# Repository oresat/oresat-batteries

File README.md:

# OreSat Battery Card

This is the battery card for the OreSat system. You can have up to four of these cards in any OreSat system, ID is set by resistors.

## Version History

- v1.0: We don't talk about v1 (EAGLE).
- v2.0: First true pack with 3D printed cell storage. Many small issues (EAGLE).
- v3.0: Flight ready pack, flown 2021-03-15 on OreSat0. Worked! (EAGLE).
- v3.1: Imported into KiCAD, small tweaks in process (KiCAD).

## Bill of Materials

- [PCBA](https://docs.google.com/spreadsheets/d/11vG1kWyrAjmbF5QJM-EhXmvQoF6O47japwYlHF802do/edit#gid=576852939)
- [Assembly](https://docs.google.com/spreadsheets/d/1GmZE2MR5q2XFSR2Y-65dwwPd7tem3i0CEjZBlCLeJBU/edit?usp=sharing)

## Mechanical CAD

- In [OnShape](https://cad.onshape.com/documents/5eda02ab87dc9021603c3619/w/adac4deb8bbe537007a3b153/e/e3b4fa777f54f6382aedf8d8).

## Technical Information

- 2 independent 2S1P 18650 battery packs (4 batteries total, in 2 packs). Each pack has:
   - Battery protection circuitry for charge and discharge control for each 2S1P pack
   - MAX17500 fuel gauge with cell balancing and cell temperature monitoring
- 3D printed battery holder, designed for CRP Windform SLS Nylon material (OK with Form3 Flame Retardant Resin).
- Positive battery lead disconnection switches (with room for plunger assemblies that go through OreSat +/-X rails).
- Satellite shutdown switches (!SHUTDOWN) (with room for plunger assemblies that go through OreSat +/-X rails).
- Flexible polyimide heater tapes to keep batteries above 0 C
- STM32F091 microcontroller (controlled by the OreSat Power Domain) to interface everything to the CAN bus

## TRANSITION DOCUMENT
Documentation is moving to [Google Docs](https://docs.google.com/document/d/1yaPGtJSM5RQG5k7sVpsDxBkVu4CHtm4LMNnisgOaNRg/edit#heading=h.gjdgxs). The rest of this readme will be integrated later.

## OreSat Vbus
OreSat main power bus is just our 2S Li Ion battery pack, which we've defined as 6.0 V minimum, 7.2 V typical, and 8.4 V maximum. Everything is directly connected to that bus, including:

- Other Oreat battery cards. For >= 2U CubeSats, you'll probably have at least two battery cards.
- All solar panels. Thus the solar panels see the direct battery voltage and can dump directly into the battery packs, thus doing _actual_ MPPT.
- All loads.

## Battery Card Topology
Confusingly, Each OreSat battery card has 2 independent battery packs on it. Each pack is made of a 2S1P 18650 LiPo cell pack. So it's a 2x2S1P if you will. Despite this, each card is independent and the OPD is fully capable of functioning with only one active card.

We decided to separate the packs instead of combining them into a single 2S2P pack for the sake of redundancy, we can lose one cell and the other pack can still provide power to the OPD, as opposed to losing an entire card from a single cell failure.  This design does come with the added drawbacks of extra overhead in the form of requiring more charge protection and fuel gauge circuitry.

## Charge/Discharge Protection
We are using Ablic S8209 to monitor our cell voltage levels and disable charging if the cell voltage goes above the predetermined overcharging threshold or disable discharging if the cell voltage goes below a predetermined discharging threshold.

The S8209 has two inputs that, if activated, will trigger the either the over-charge or under-charge protection to activate.  This allows us to daisy chain these chips together, so that each cell has its own charge protection IC.  It also allows us to connect them to a GPIO on an onboard microcontroller so that we can manually disable charging or discharging functionality if needed.  Below is a state diagram that depicts the desired behavior of our charging and discharging protection circuit

The output of the S8209 uses an internal N-channel MOSFET, which has the potential to latch from radiation exposure.   To combat this, we have P-channel MOSFETS in series with the VDD of each S8209, the gate of the MOSFET is connected to our onboard microcontroller, so that we can periodically power cycle the S8209 and clear the N-channel latch.

The actual control of charge and discharge are done using Linear LTC4412 ideal diode controllers. Totally bizarre, but indepdenently controllable!

## Fuel Gauge and Cell Health Monitoring
Each 2S1P battery back will have two MAX17205 fuel gauges to monitor the packs current state of charge, and the long term health of the battery.  Each MAX17205 will be reporting both the direct State of charge (in mAh) and the percentage over I2C to our M0, compensating for factors such as cell degradation and temperature ranges.  We are still testing the accuracy of the MAX17205's compensation algorithm's for extreme charge levels and temperature in our lab.  At this point we don't know how much we should be relying on these compensation algorithms, they could be amazing! Or horrible! We don't know! Yay science!

Each fuel gauge is also monitoring the battery temperatures with a single internal sensor and two external thermistors (we are still determining the best position for these thermistors).  This gives us a wackton of data which is good because we are data hoarders.

Finally the MAX17205 also does cell balancing, which we'll enable while charging.

## Heaters
Thermal models of both 1U and 2U CubeSats show an average "passive" battery temperature of ~ -10 C). That's not good. We can't charge the battery below 0 C. So we've added heaters to heat up the batteries when charging if necessary.

We're using two Minco HK6903 heaters in parallel. They have "vacuum OK" (apparently?) urethane PSA that we'll use to attach them to the batteries. Note that they're 12.7 x 100 mm, and each heater goes across both batteries. At 49 ohms +/- 10% each, that's 25 ohms in parallel. Unclear on the heater's tempco. We'll ignore for now.

- At 8.4V, that's 336 mA = 2.8 W (at 100% DC)
- At 6.0V, that's 240 mA = 1.4 W (at 100% DC)
- We can of course PWM them and reduce the power as necessary

With that much current draw, we're going to need to modify the OPD circuit breaker to allow more current.

## Batteries

- Tenergy model "30005-0 (ICR 18650-2600, LR1865SK)"
- Rated at 2600 mAh
- Max voltage: 4.2 V
- Typical voltage: 3.6 V
- Minimum voltage: 2.75 V
- Maximum charge current: 1.25 A
   - 0 - 45 C only
- Maximum discharge Current:
   - -20 - 5 C = 1.25 A
   -  5 - 45 C = 5 A
   - 45 - 60 C = 3.75 A

### Temperature

Just to summarize the battery temperature operational range:

- Cell temperature < -20 C -- DEAD
- Cell temperature < 0 C -- DISCHARGE ONLY
- Cell temperature < 45 C -- NORMAL OPERATION
- Cell temperature > 45 C-- DISCHARGE ONLY
- Cell temperature > 60 C-- DEAD

### Cell failure (short)

- Short will plummet battery to < 2.5V (Vlvco) and S-8209 will disconnect the battery from discharging but not charging

## Battery pack behaviors (circuitry + firmware)

- Automatic discharge if > 6.0 V
- Automatic slow charge if < 8.4 V
- Fast charge if battery pack within ~ 0.5 V of other batteries

## Hacking the OPD Circuit Breaker

The OPD circuit breaker is supposed to trip at 300 mA without any division at the current output. Since the headers could pull up to 336, we need to probably go up to that plus 50 mA. So we put in a 10K and 20K to make a 0.66 divider and an N CH MOSFET to turn on the divider on the signal "MOARPWR". Asserting MOARPWR should give you up to 400 mA.

## LICENSE

Copyright Portland State Aerospace Society 2020.

This documentation describes Open Hardware and is licensed under the CERN OHL v. 1.2.

You may redistribute and modify this documentation under the terms of the CERN OHL v.1.2. [http://ohwr.org/cernohl](http://ohwr.org/cernohl). This documentation is distributed WITHOUT ANY EXPRESS OR IMPLIED WARRANTY, INCLUDING OF MERCHANTABILITY, SATISFACTORY QUALITY AND FITNESS FOR A PARTICULAR PURPOSE. Please see the CERN OHL v.1.2 for applicable conditions.

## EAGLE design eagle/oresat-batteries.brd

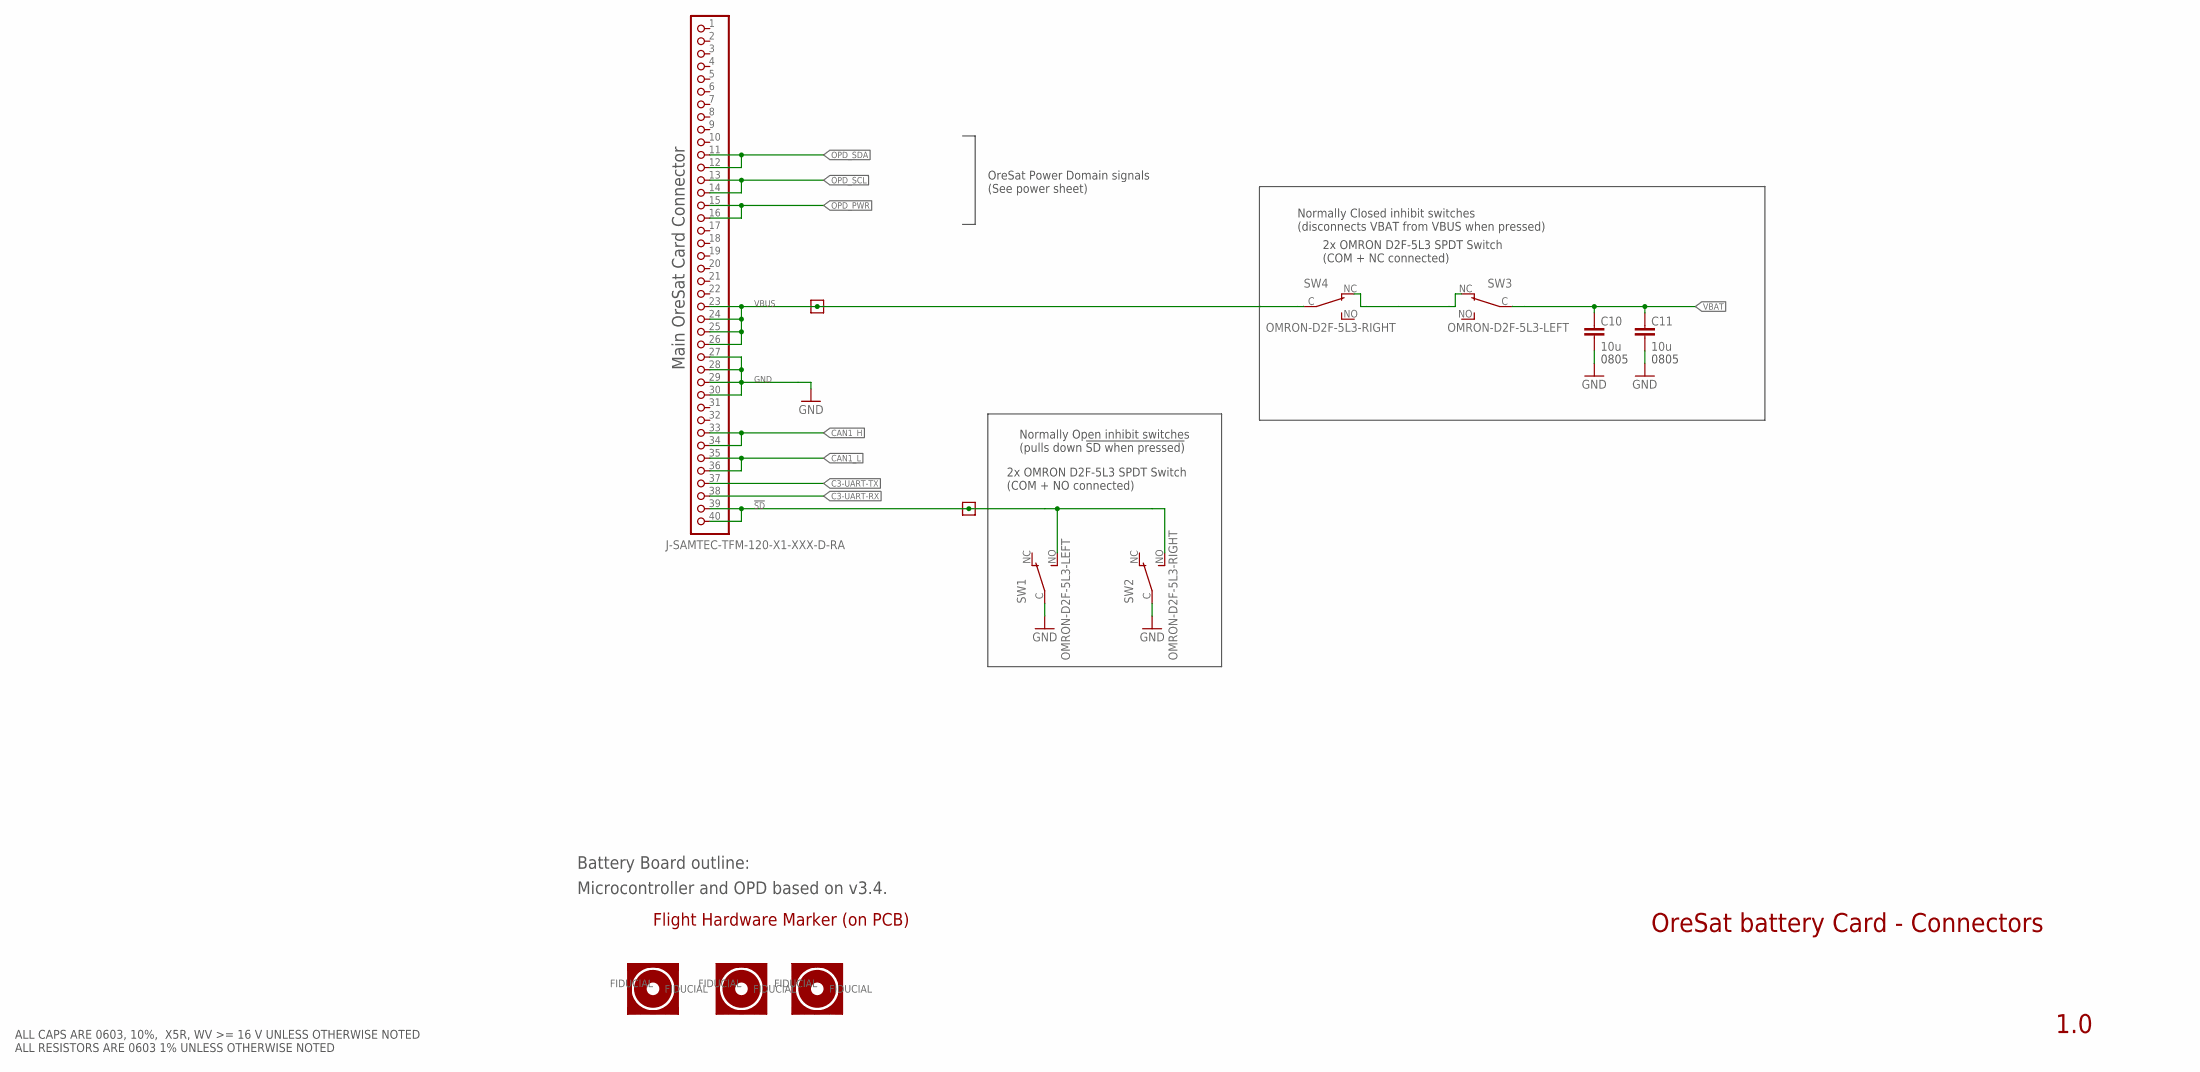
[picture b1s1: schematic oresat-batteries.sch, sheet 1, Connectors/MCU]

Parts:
C10, C11: 10u; .0805-B-NOSILK; MPN CL21A106KOFNNNE
FIDUCIAL1, FIDUCIAL2, FIDUCIAL3: FIDUCIAL-1.0X2.0
J1: J-SAMTEC-TFM-120-X1-XXX-D-RA; MPN TFM-120-01-L-D-RA
SW1, SW3: OMRON-D2F-5L3-LEFT; D2F-L3-D-HORIZONTAL-L
SW2, SW4: OMRON-D2F-5L3-RIGHT; D2F-L3-D-HORIZONTAL-R
TP25, TP57: TEST-POINT-LARGE-SQUARE; 1X01
U$1: FLIGHMARKERNEW; FLIGHTMARKER_NEW_BOARDS

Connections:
!SD: J1.39, J1.40, SW1.NO, SW2.NO, TP57.1; also elsewhere on the board
C3-UART-RX: J1.38; also elsewhere on the board
C3-UART-TX: J1.37; also elsewhere on the board
CAN1_H: J1.33, J1.34; also elsewhere on the board
CAN1_L: J1.35, J1.36; also elsewhere on the board
GND: C10.2, C11.2, J1.27, J1.28, J1.29, J1.30, SW1.C (COM), SW2.C (COM); also elsewhere on the board
INTERSW: SW3.NC, SW4.NC
OPD_PWR: J1.15, J1.16; also elsewhere on the board
OPD_SCL: J1.13, J1.14; also elsewhere on the board
OPD_SDA: J1.11, J1.12; also elsewhere on the board
VBAT: C10.1, C11.1, SW3.C (COM); also elsewhere on the board
VBUS: J1.23, J1.24, J1.25, J1.26, SW4.C (COM), TP25.1; also elsewhere on the board

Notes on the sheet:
OreSat battery Card - Connectors
1.0
Main OreSat Card Connector
OreSat Power Domain signals (See power sheet)
Battery Board outline:
Microcontroller and OPD based on v3.4.
ALL CAPS ARE 0603, 10%, X5R, WV >= 16 V UNLESS OTHERWISE NOTED ALL RESISTORS ARE 0603 1% UNLESS OTHERWISE NOTED
Normally Open inhibit switches (pulls down !SD when pressed)
2x OMRON D2F-5L3 SPDT Switch (COM + NO connected)
Normally Closed inhibit switches (disconnects VBAT from VBUS when pressed)
2x OMRON D2F-5L3 SPDT Switch (COM + NC connected)
0805

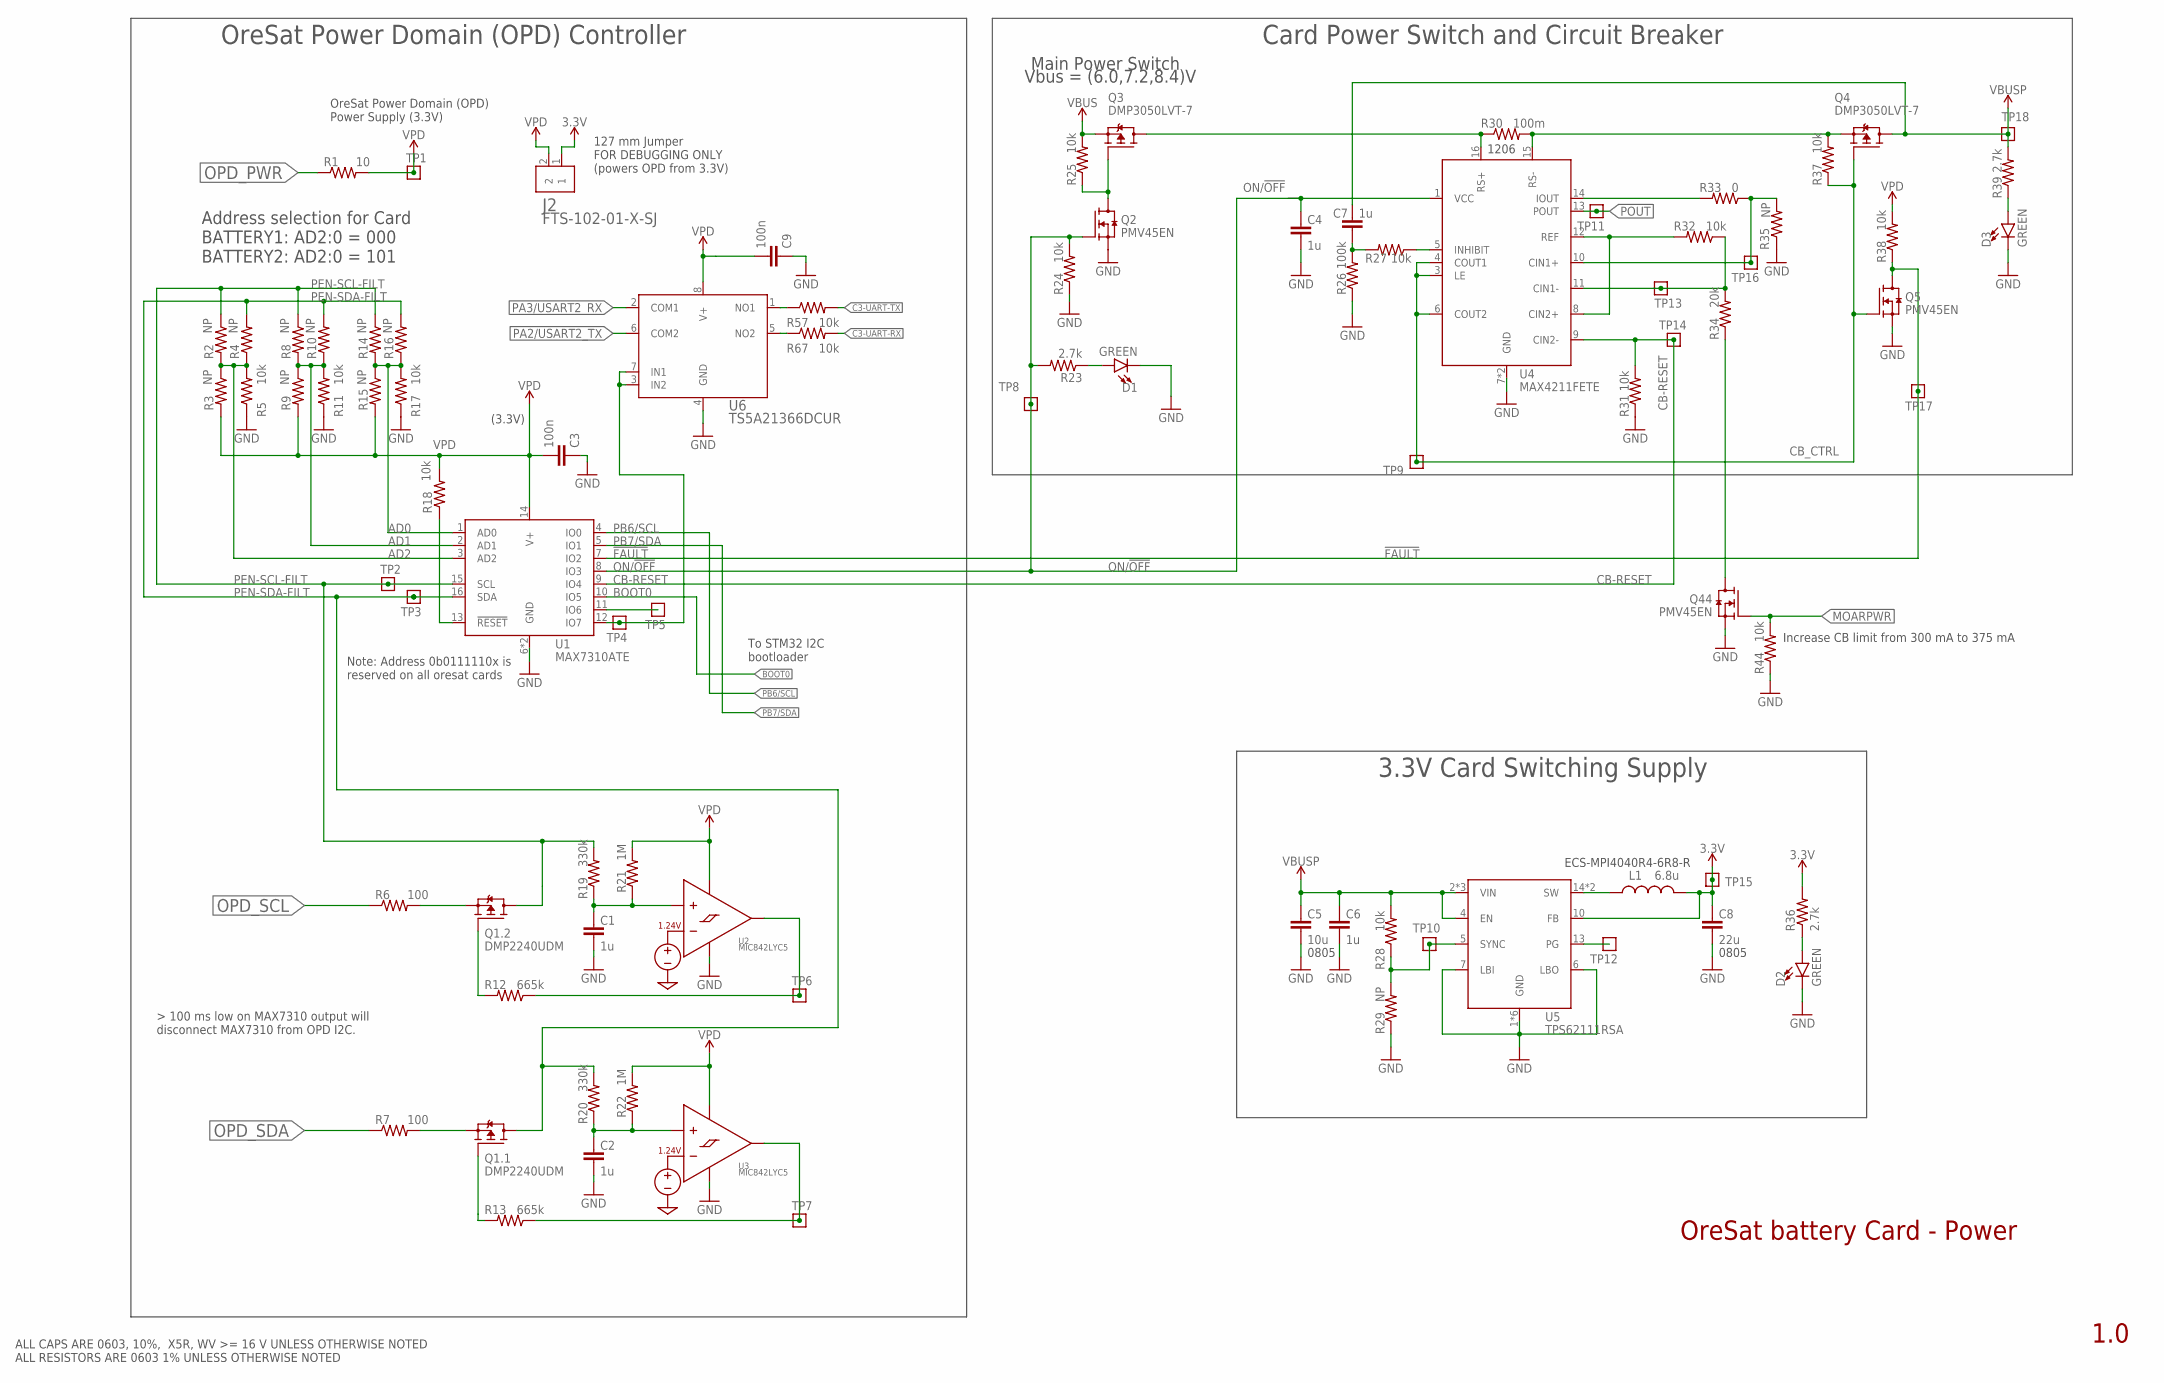
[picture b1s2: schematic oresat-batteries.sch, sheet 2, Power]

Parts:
C1, C2, C4: 1u; .0603-C-NOSILK; MPN CL10B105MO8NNWC
C3, C9: 100n; .0603-C-NOSILK; MPN CL05B104KO5NNNC
C5: 10u; .0805-B-NOSILK; MPN CL21A106KOFNNNE
C6: 1u; .0603-C-NOSILK; MPN CC0603KRX7R7BB105
C7: 1u; .0603-C-NOSILK
C8: 22u; .0805-B-NOSILK; MPN GRM21BR61A226ME51L
D1: GREEN; LED-0603; MPN IN-S63AT5A
D2, D3: GREEN; LED-0603; MPN SML-E12M8WT86
J2: FTS-102-01-X-SJ; SAMTEC-FTS-102-01-X-S
L1: 6.8u; ECS-MPI4040; MPN ECS-MPI4040R4-6R8-R
Q1: DMP2240UDM; SOT23-6; MPN DMP2240UDM
Q2, Q5, Q44: PMV45EN; SOT23-3; MPN PMV45EN2R
Q3, Q4: DMP3050LVT-7; SOT23-6; MPN DMP3050LVT-7
R1: 10; .0603-C-NOSILK; MPN RC0603FR-0710RL
R2, R3, R4, R8, R9, R10, R14, R15, R16: NP; .0603-C-NOSILK; MPN RC0603FR-07665KL
R5, R11, R17, R57, R67: 10k; .0603-C-NOSILK; MPN RC0603FR-07665KL
R6, R7: 100; .0603-C-NOSILK; MPN RC0603FR-07100RL
R12, R13: 665k; .0603-C-NOSILK; MPN RC0603FR-07665KL
R18, R24, R25, R28, R31, R32, R37, R38, R44: 10k; .0603-C-NOSILK; MPN RC0603FR-0710KL
R19, R20: 330k; .0603-C-NOSILK; MPN CRGCQ0603F330K
R21, R22: 1M; .0603-C-NOSILK; MPN RC0603FR-071ML
R23, R36, R39: 2.7k; .0603-C-NOSILK; MPN CRGCQ0603F2K7
R26: 100k; .0603-C-NOSILK; MPN RC1005F6653CS
R27: 10k; .0603-C-NOSILK; MPN RC1005F6653CS
R29, R35: NP; .0603-C-NOSILK; MPN RC1005F6653CS
R30: 100m; 1206-C; MPN CSR1206FTR100
R33: 0; .0603-C-NOSILK; MPN RC0603JR-070RL
R34: 20k; .0603-C-NOSILK; MPN RR0816P-203-D
TP1, TP2, TP3, TP4, TP5, TP6, TP7, TP8, TP9, TP10, TP11, TP12, TP13, TP14, TP15, TP16, TP17, TP18: TEST-POINT-LARGE-SQUARE; 1X01
U1: MAX7310ATE; QFN65P400X400X80-17T210; MPN MAX7310ATE
U2: MIC842LYC5; SC70-5; MPN MIC842LYC5-TR
U3: MIC842LYC5; SC70-5
U4: MAX4211FETE; QFN65P400X400X80-17T210; MPN MAX4211FETE
U5: TPS62111RSA; S-PVQFN-16; MPN TPS62111RSA
U6: TS5A21366DCUR; DCU0008A_N

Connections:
3.3V: C8.1, J2.1, L1.2, R36.2, TP15.1, U5.10 (FB); also elsewhere on the board
!FAULT: Q5.3 (D), R38.1, TP17.1, U1.7 (IO2)
AD0: R14.2, R15.1, R16.1, R17.2, U1.1 (AD0)
AD1: R8.2, R9.1, R10.1, R11.2, U1.2 (AD1)
AD2: R2.2, R3.1, R4.1, R5.2, U1.3 (AD2)
BOOT0: U1.10 (IO5); also elsewhere on the board
C3-UART-RX: R67.2; also elsewhere on the board
C3-UART-TX: R57.2; also elsewhere on the board
CB-RESET: R31.2, TP14.1, U1.9 (IO4), U4.9 (CIN2-)
CB_CTRL: Q4.3 (G), Q5.1 (G), R37.1, TP9.1, U4.3 (LE), U4.4 (COUT1), U4.6 (COUT2)
GND: C1.2, C2.2, C3.1, C4.2, C5.2, C6.2, C8.2, C9.1, D1.C, D2.C, D3.C, Q2.2 (S), Q5.2 (S), Q44.2 (S), R5.1, R11.1, R17.1, R24.1, R26.1, R29.1, R31.1, R35.1, R44.1, U1.6 (GND), U1.EPAD (GND), U2.2 (GND), U3.2 (GND), U4.7 (GND), U4.EPAD (GND), U5.1 (GND), U5.6 (LBO), U5.7 (LBI), U5.9 (GND), U5.11 (GND), U5.12 (GND), U5.16 (GND), U5.PAD (GND), U6.4 (GND); also elsewhere on the board
IOUT1: R33.2, U4.14 (IOUT)
MOARPWR: Q44.1 (G), R44.2; also elsewhere on the board
unnamed: R57.1, U6.1 (NO1)
unnamed: R67.1, U6.5 (NO2)
unnamed: D3.A, R39.1
unnamed: D2.A, R36.1
unnamed: R18.1, U1.13 (!RESET)
unnamed: Q2.3 (D), Q3.3 (G), R25.1
unnamed: Q3.1 (D), Q3.2 (D), Q3.5 (D), Q3.6 (D), R30.1, U4.16 (RS+)
unnamed: Q1.1 (G), R13.2
unnamed: Q44.3 (D), R34.1
unnamed: Q1.3 (G), R12.2
unnamed: R33.1, R35.2, TP16.1, U4.10 (CIN1+)
unnamed: R32.1, R34.2, TP13.1, U4.11 (CIN1-)
unnamed: R32.2, U4.8 (CIN2+), U4.12 (REF)
unnamed: R27.1, U4.5 (INHIBIT)
unnamed: C7.1, R26.2, R27.2
unnamed: Q4.4 (S), R30.2, R37.2, U4.15 (RS-)
unnamed: D1.A, R23.1
unnamed: Q1.5 (S), R7.2
unnamed: R13.1, TP7.1, U3.4 (OUT)
unnamed: TP5.1, U1.11 (IO6)
unnamed: Q1.2 (S), R6.2
unnamed: R12.1, TP6.1, U2.4 (OUT)
unnamed: C1.1, R19.1, R21.1, U2.1 (INP)
unnamed: C2.1, R20.1, R22.1, U3.1 (INP)
unnamed: TP4.1, U1.12 (IO7), U6.3 (IN2), U6.7 (IN1)
ON/!OFF: C4.1, Q2.1 (G), R23.2, R24.2, TP8.1, U1.8 (IO3), U4.1 (VCC)
OPD_PWR: R1.1; also elsewhere on the board
OPD_SCL: R6.1; also elsewhere on the board
OPD_SDA: R7.1; also elsewhere on the board
PA2/USART2_TX: U6.6 (COM2); also elsewhere on the board
PA3/USART2_RX: U6.2 (COM1); also elsewhere on the board
PB6/SCL: U1.4 (IO0); also elsewhere on the board
PB7/SDA: U1.5 (IO1); also elsewhere on the board
PEN-SCL-FILT: Q1.4 (D), R2.1, R8.1, R14.1, R19.2, TP2.1, U1.15 (SCL)
PEN-SDA-FILT: Q1.6 (D), R4.2, R10.2, R16.2, R20.2, TP3.1, U1.16 (SDA)
POUT: TP11.1, U4.13 (POUT); also elsewhere on the board
TPS62111-PG1: TP12.1, U5.13 (PG)
TPS62111-SYNC1: R28.1, R29.2, TP10.1, U5.5 (SYNC)
TPS62111_SW1: L1.1, U5.14 (SW), U5.15 (SW)
VBUS: Q3.4 (S), R25.2; also elsewhere on the board
VBUSP: C5.1, C6.1, C7.2, Q4.1 (D), Q4.2 (D), Q4.5 (D), Q4.6 (D), R28.2, R39.2, TP18.1, U5.2 (VIN), U5.3 (VIN), U5.4 (EN), U5.8 (VIN); also elsewhere on the board
VPD: C3.2, C9.2, J2.2, R1.2, R3.2, R9.2, R15.2, R18.2, R21.2, R22.2, R38.2, TP1.1, U1.14 (V+), U2.5 (VDD), U3.5 (VDD), U6.8 (V+)

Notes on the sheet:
OreSat battery Card - Power
1.0
Main Power Switch
Address selection for Card
(3.3V)
0805
ECS-MPI4040R4-6R8-R
Vbus = (6.0,7.2,8.4)V
OreSat Power Domain (OPD) Power Supply (3.3V)
OreSat Power Domain (OPD) Controller
3.3V Card Switching Supply
Card Power Switch and Circuit Breaker
Note: Address 0b0111110x is reserved on all oresat cards
To STM32 I2C bootloader
1206
ALL CAPS ARE 0603, 10%, X5R, WV >= 16 V UNLESS OTHERWISE NOTED ALL RESISTORS ARE 0603 1% UNLESS OTHERWISE NOTED
Increase CB limit from 300 mA to 375 mA
127 mm Jumper FOR DEBUGGING ONLY (powers OPD from 3.3V)
BATTERY1: AD2:0 = 000 BATTERY2: AD2:0 = 101

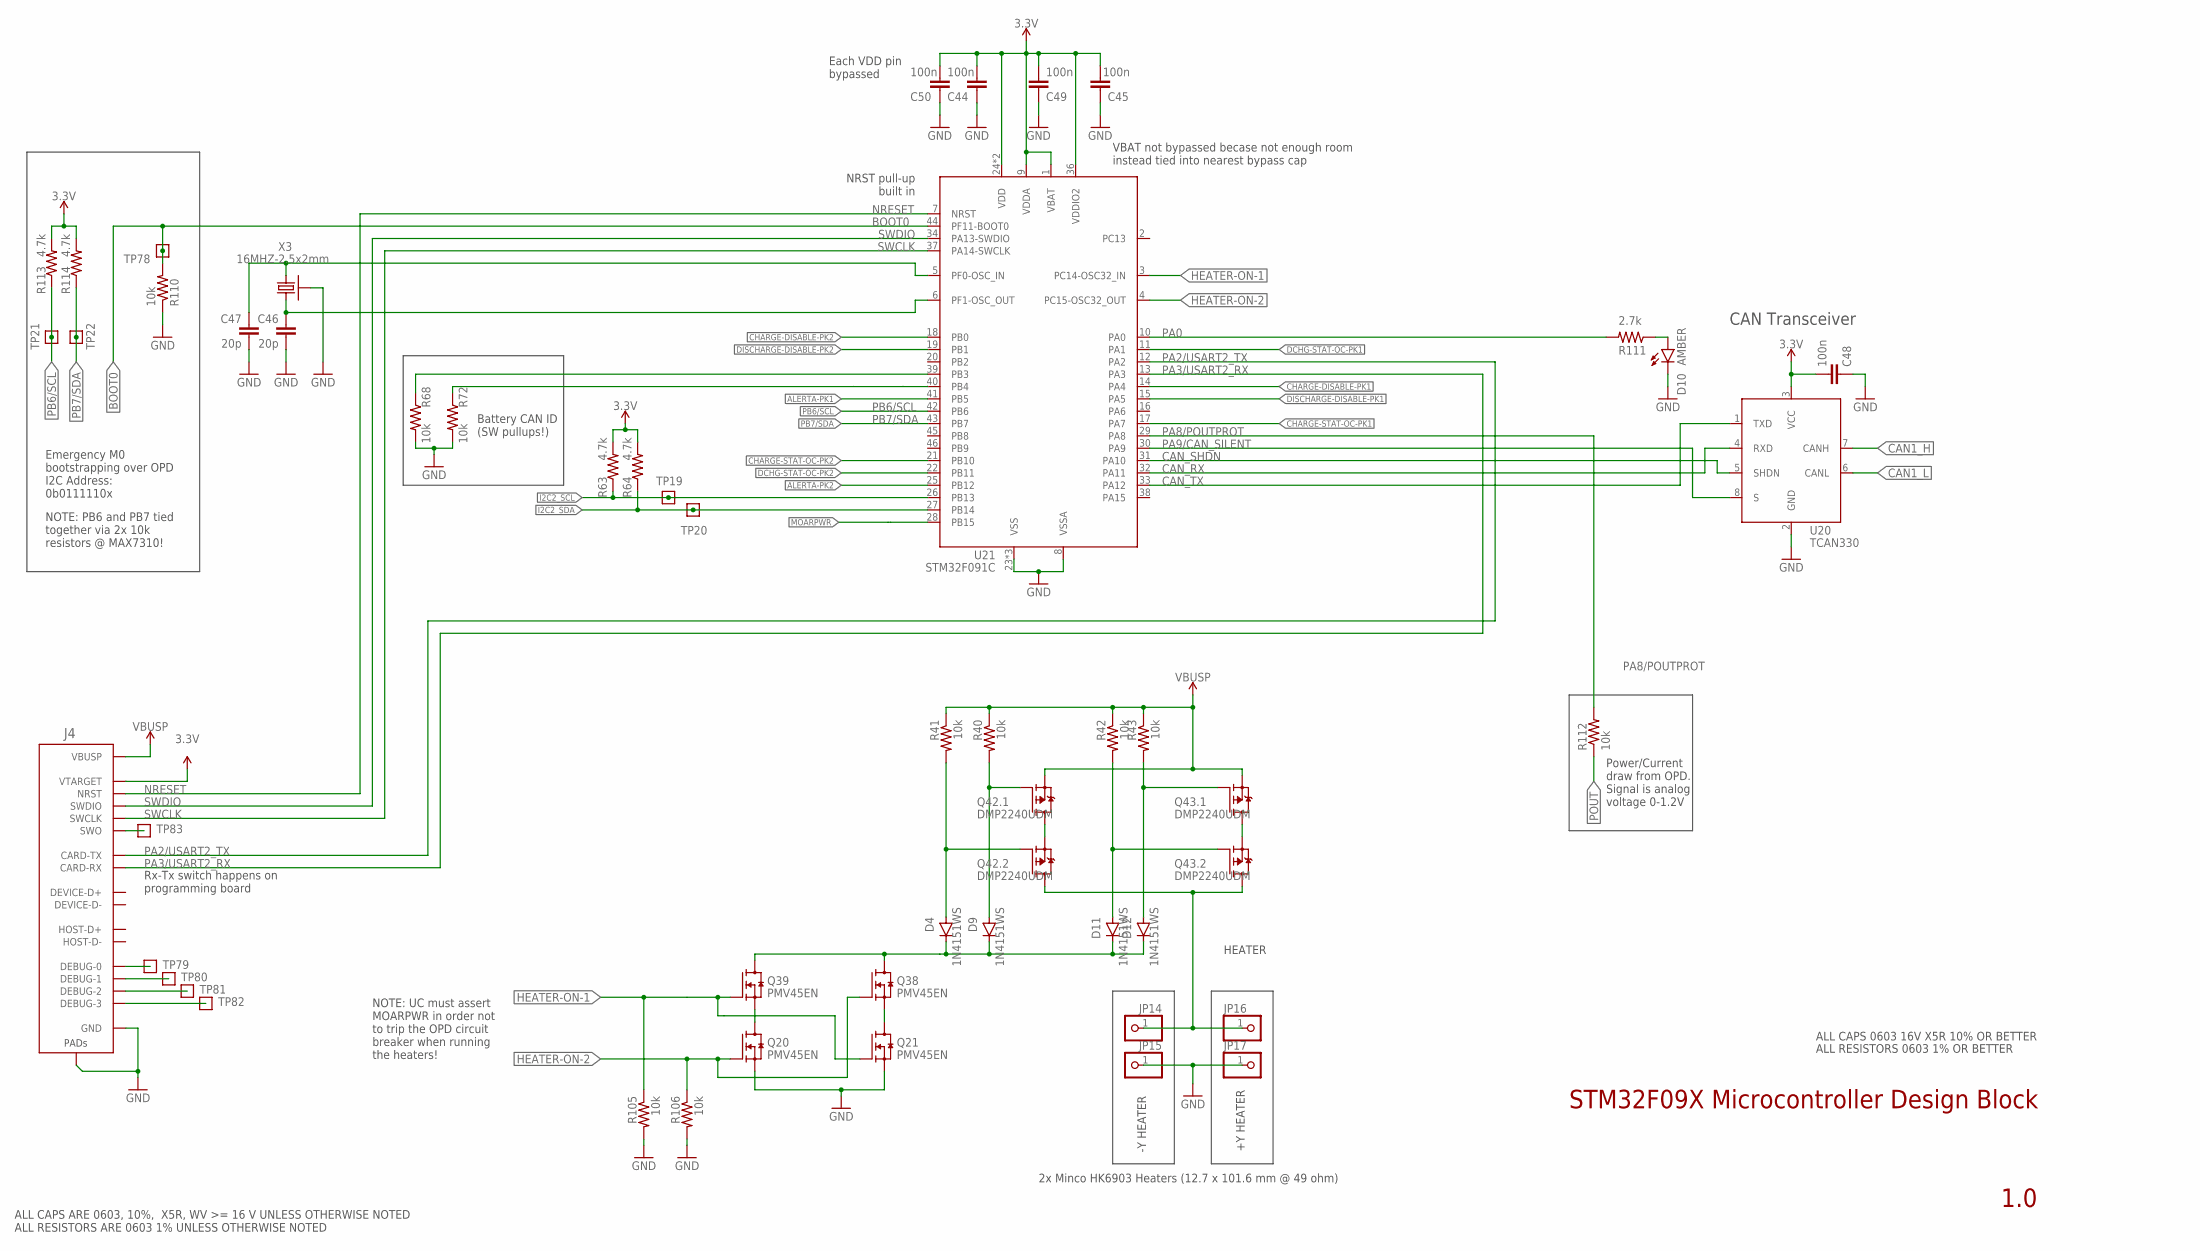
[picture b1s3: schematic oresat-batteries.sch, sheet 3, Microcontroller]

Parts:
C44, C45, C48, C49, C50: 100n; .0603-C-NOSILK; MPN C0603C104M4RACTU
C46, C47: 20p; .0603-C-NOSILK; MPN CC0603JRNPO9BN200
D4, D9, D11, D12: 1N4151WS; SOD323-R; MPN 1N4151WS-E3-08
D10: AMBER; LED-0603; MPN IN-S63AT5A
J4: ORESAT-DEBUG-CONNECTOR-ALL; TE_2-1734592-0; MPN 2-1734592-0
JP14, JP15, JP16, JP17: PINHD-1X1; 1X01
Q20, Q21, Q38, Q39: PMV45EN; SOT23-3
Q42, Q43: DMP2240UDM; SOT23-6
R40, R41, R42, R43, R105, R106, R110, R112: 10k; .0603-C-NOSILK; MPN RC0603FR-0710KL
R63, R64, R113, R114: 4.7k; .0603-C-NOSILK; MPN RR0816P-472-D
R68, R72: 10k; .0603-C-NOSILK; MPN RR0816P-472-D
R111: 2.7k; .0603-C-NOSILK; MPN CRGCQ0603F2K7
TP19, TP20, TP21, TP22, TP78, TP79, TP80, TP81, TP82, TP83: TEST-POINT-LARGE-SQUARE; 1X01
U20: TCAN330; SOT23-8_TI-DCN; MPN TCAN330GDCNT
U21: STM32F091C; MPN STM32F091CBT6
X3: 16MHZ-2.5x2mm; CRYSTAL_2.5X2; MPN ECS-160-10-36Q-ES-TR

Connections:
3.3V: C44.2, C45.2, C48.2, C49.2, C50.2, J4.11 (VTARGET), R63.2, R64.2, R113.2, R114.2, U20.3 (VCC), U21.1 (VBAT), U21.9 (VDDA), U21.24 (VDD), U21.36 (VDDIO2), U21.48 (VDD); also elsewhere on the board
ALERTA-PK1: U21.41 (PB5); also elsewhere on the board
ALERTA-PK2: U21.25 (PB12); also elsewhere on the board
BOOT0: R110.2, TP78.1, U21.44 (PF11-BOOT0); also elsewhere on the board
CAN1_H: U20.7 (CANH); also elsewhere on the board
CAN1_L: U20.6 (CANL); also elsewhere on the board
CAN_RX: U20.4 (RXD), U21.32 (PA11)
CAN_SHDN: U20.5 (SHDN), U21.31 (PA10)
CAN_TX: U20.1 (TXD), U21.33 (PA12)
CHARGE-DISABLE-PK1: U21.14 (PA4); also elsewhere on the board
CHARGE-DISABLE-PK2: U21.18 (PB0); also elsewhere on the board
CHARGE-STAT-OC-PK1: U21.17 (PA7); also elsewhere on the board
CHARGE-STAT-OC-PK2: U21.21 (PB10); also elsewhere on the board
CRYSTALIN2: C47.1, U21.5 (PF0-OSC_IN), X3.1
CRYSTALOUT2: C46.1, U21.6 (PF1-OSC_OUT), X3.3 (2)
DCHG-STAT-OC-PK1: U21.11 (PA1); also elsewhere on the board
DCHG-STAT-OC-PK2: U21.22 (PB11); also elsewhere on the board
DISCHARGE-DISABLE-PK1: U21.15 (PA5); also elsewhere on the board
DISCHARGE-DISABLE-PK2: U21.19 (PB1); also elsewhere on the board
GND: C44.1, C45.1, C46.2, C47.2, C48.1, C49.1, C50.1, D10.C, J4.3 (GND), J4.6 (GND), J4.9 (GND), J4.PAD1 (PAD), J4.PAD2 (PAD), JP15.1, JP17.1, Q20.2 (S), Q21.2 (S), R68.2, R72.2, R105.2, R106.2, R110.1, U20.2 (GND), U21.8 (VSSA), U21.23 (VSS), U21.35 (VSS), U21.47 (VSS), X3.2 (SHIELD), X3.4 (SHIELD); also elsewhere on the board
HEATER: JP14.1, JP16.1, Q42.4 (D), Q43.4 (D)
HEATER-ON-1: Q21.1 (G), Q39.1 (G), R105.1, U21.3 (PC14-OSC32_IN)
HEATER-ON-2: Q20.1 (G), Q38.1 (G), R106.1, U21.4 (PC15-OSC32_OUT)
I2C2_SCL: R63.1, TP19.1, U21.26 (PB13); also elsewhere on the board
I2C2_SDA: R64.1, TP20.1, U21.27 (PB14); also elsewhere on the board
MOARPWR: U21.28 (PB15); also elsewhere on the board
unnamed: D11.A, Q43.3 (G), R42.2
unnamed: D4.A, Q42.3 (G), R41.2
unnamed: Q42.2 (S), Q42.6 (D)
unnamed: Q43.2 (S), Q43.6 (D)
unnamed: R68.1, U21.39 (PB3)
unnamed: D12.A, Q43.1 (G), R43.2
unnamed: D9.A, Q42.1 (G), R40.2
unnamed: D4.C, D9.C, D11.C, D12.C, Q38.3 (D), Q39.3 (D)
unnamed: Q20.3 (D), Q39.2 (S)
unnamed: Q21.3 (D), Q38.2 (S)
unnamed: R72.1, U21.40 (PB4)
unnamed: D10.A, R111.1
unnamed: J4.20 (DEBUG-3), TP82.1
unnamed: J4.19 (DEBUG-2), TP81.1
unnamed: J4.18 (DEBUG-1), TP80.1
unnamed: J4.17 (DEBUG-0), TP79.1
unnamed: J4.16 (SWO), TP83.1
NRESET: J4.10 (NRST), U21.7 (NRST)
PA0: R111.2, U21.10 (PA0)
PA2/USART2_TX: J4.13 (CARD-TX), U21.12 (PA2); also elsewhere on the board
PA3/USART2_RX: J4.12 (CARD-RX), U21.13 (PA3); also elsewhere on the board
PA8/POUTPROT: R112.2, U21.29 (PA8)
PA9/CAN_SILENT: U20.8 (S), U21.30 (PA9)
PB6/SCL: R113.1, TP21.1, U21.42 (PB6); also elsewhere on the board
PB7/SDA: R114.1, TP22.1, U21.43 (PB7); also elsewhere on the board
POUT: R112.1; also elsewhere on the board
SWCLK: J4.15 (SWCLK), U21.37 (PA14-SWCLK)
SWDIO: J4.14 (SWDIO), U21.34 (PA13-SWDIO)
VBUSP: J4.1 (VBUSP), J4.2 (VBUSP), Q42.5 (S), Q43.5 (S), R40.1, R41.1, R42.1, R43.1; also elsewhere on the board

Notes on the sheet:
ALL CAPS ARE 0603, 10%, X5R, WV >= 16 V UNLESS OTHERWISE NOTED ALL RESISTORS ARE 0603 1% UNLESS OTHERWISE NOTED
NRST pull-up built in
CAN Transceiver
1.0
Emergency M0 bootstrapping over OPD I2C Address: 0b0111110x
NOTE: PB6 and PB7 tied together via 2x 10k resistors @ MAX7310!
Power/Current draw from OPD. Signal is analog voltage 0-1.2V
Each VDD pin bypassed
VBAT not bypassed becase not enough room instead tied into nearest bypass cap
Rx-Tx switch happens on programming board
STM32F09X Microcontroller Design Block
ALL CAPS 0603 16V X5R 10% OR BETTER
ALL RESISTORS 0603 1% OR BETTER
HEATER
-Y HEATER
+Y HEATER
2x Minco HK6903 Heaters (12.7 x 101.6 mm @ 49 ohm)
NOTE: UC must assert MOARPWR in order not to trip the OPD circuit breaker when running the heaters!
Battery CAN ID (SW pullups!)

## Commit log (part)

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2016-09-27 Added link to design docs
2016-09-27 Changed link to public view-only.
2017-04-13 Overdue Dump, Added files, libs etc.
2017-04-13 Added crystal, CAN transciever
2017-04-13 Added Parts Selection md
2017-04-14 Changed board to real max dimensions. Added 40pin connector
2017-04-14 Removed locks!
2017-04-14 Added 40 pin for real this time.
2017-04-17 Added block diagram
2017-04-18 Swapped fuel gauge for ti BQ27500
2017-04-25 Replaced BQ27500 with STC300lST
2017-04-26 Added potential battery to schematic
2017-05-04 Started rough layout of boards. Updated design docs (see google docs)
2017-05-06 Finished first draft of schematics.
2017-06-21 Minor clean up, added debug board, serial marker
2017-06-23 Added, resistive heater, half of shutdown circuitry, connected DIG_IOx and SYS_EN pins.
2017-06-23 Fixed Shutdown Circuit, Added more ground pins, cleaned up schematic
2017-06-23 Added TP and nominal V for shutoff
2017-06-23 Named missing NETS
2017-06-23 Replaced Shutdown with new circuitry that will actually work... maybe.
2017-06-24 Cleaned up schematic
2017-06-24 Removed unecessary files and directories.
2017-06-30 Cleaned up schematic, moved STC sense resistor to proper place.
2017-06-30 Schematic Cleanup, added labels and isolated chips visually
2017-06-30 Cleaned up schematci, added frame.
2017-07-01 More cleaning.
2017-07-07 Fixed V- pin on STC
2017-07-07 Fixed TP non-connect issue
2017-07-07 Added ignore for locks. Cleaned up schematic.
2017-07-07 Cleaned up schematic, added filter comp values
2017-07-07 Added comp values
2017-07-08 Cleaned schematic
2017-07-08 First battery board design review. Updated ADP symbol, package, and schematic.
2017-07-11 Cleaned up schematic, reverted to previous configuration for ADP
2017-07-12 Added 3.3V switching power supply
2017-08-16 Added v1.1 to batteries, updated inverter choices in docs.
2017-09-15 Added ideal diodes and new fuel gauge
2017-09-20 Updated batteries with latest OreSat card and connector.
2017-09-23 Added 4412 and toshiba P-Channel Mosfets.
2017-09-23 Added charge and discharge control, lowside shutdown, test points and finished rough v1.1 design.
2017-09-27 Added double pin header.
2017-09-28 Fixed most of the issues from design review Sept 25.
2017-09-28 Cosmetics.
2017-09-28 Cosmetics again.
2017-09-28 Cosmeticas.
2017-10-30 Updates after design review with Austin. Still some TODOs before layout.
2017-11-11 Preliminary layout.
2017-11-17 Cosmetics and polygons.
2017-11-18 Moved to OSH Park 4 layer DRU, fixed some bad/useless layers.
2017-12-04 Cosmetics, moved signals to top and bottom layer.
2017-12-10 Cosmetics, moved all power and signals from gnd layer
2017-12-10 Cleaning, removing airwires.
2018-02-12 Add Gitter badge
2018-03-15 First cleanup of batteries post-Austin going to NASA. Austiiiiinnnnnnnnn, come backgit diff ../design.mdn111git diff ../design.mdn./run More sane two sheet layout on schematic, cleaned up in and out 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
2018-09-24 Fixed body diode issue on output. Changed N to P mosfett for 'trace heater.'
2018-10-04 Assigned IO pins to circuit functions. Finished controls for heater.
2019-03-23 Last changes to previous 1 cell battery pack. Abandoning for 2 cell packs because we're weenies.
2019-03-23 New 2S2P battery boards, based on 18650 cells along with a BQ28400 battery IC.
2019-07-21 removed obsolete documentation
2019-07-21 removed accidental file
2019-07-29 update schematic with s8209 and MAX17205 chips for battery protection and control
2019-07-29 Design review of schematic. Added labels, nets to M0, shutdown circuitry, discussed power domains.
2019-08-02 Eagle updates for battery card 2.0
2019-08-02 handing over to andrew for design review, still needs newest MCAD dxf for inhibit switches
2019-08-06 Updated battery board to latest outline (via oresat-cards.lbr), fixed ground planes, fixed main connector, done for now.
2019-08-06 started revising battery board documenation
2019-08-12 added state diagram, more datasheets, starting moving from 2S2P to 2S1P packs
2019-08-15 version 2.0 of battery card, moved to 2S1P packs, extra battery charge and fuel gauge circuitry, moved to 4 layer board
2019-08-15 png of state diagram
2019-08-15 documentation on S8209 charge protection circuit
2019-08-20 "auto-generated from update_repos.py"
2019-08-24 documentation for the fuel gauge
2019-12-29 New battery schematic and board. New Ablic and SD topology, with battery disconnect circuitry. Updated to Microcontroller and OPD v3.4.
2020-01-13 One 2S1P pack prototype, to be used with a protocard!
2020-01-13 v1.0 of the battery pack prototype board
2020-01-13 Last minute polish on the board.
2020-01-14 Finalized battery prototype, choose parts, made BOM, ordered!
2020-04-16 Latest OreSat battery board form factor, working with Oleg. Now with less tabs, and more slots, and more room
2020-04-17 Latest battery holder DXF with more simple layout and more thermal resistance to frame. Updated battery circuitry from try #3 of the battery prototype. Only one pack layed out, checking in anyway.
2020-04-18 Battery board v1 schematic and layout complete. Lots of checking and polishing left to do, but OMG, finally.
2020-04-18 Now with 100% realistic SOT23-3 transistors and more cleanup.
2020-04-18 More cleanup; added more space in battery tab stitching, and made them hopefully more sane?
2020-04-18 Renumbered parts using built-in renumber tool.
2020-07-12 First real thoughts on inhibit switches.
2020-07-28 Updated battery card with Oleg's drawings; about to upgrade processors.
2020-07-29 New F091 processor. Battery layout done! Still needs polishing.
2020-08-03 Some feedback from design review; more text, 100k instead of 10k for some transistors, still missing heaters.
2020-08-16 Temporary check in; still need to complete heater circuits.
2020-08-17 Updated README, killed design documents. Also, finished layout. Still need to polish, but heater is layed out and doesn't seem to be terrible.
2020-08-17 Polished battery board.
2020-08-17 More documentation cleanup
2020-08-17 Oh, uh, yeah, include the CERN OHL
2020-08-17 remove old prototype files
2020-08-25 Added tolerance note to heaters.
2020-08-29 fixed a couple left over attributes and formatted BOM
2020-09-14 Made sure all files are tracked in git.
2020-12-29 Added PDF of block diagram
2020-12-29 Removed weird file
2020-12-29 Added weird file to .gitignore.
2021-03-01 OreSat Battery Card v2.0
    Changes based on finally fixing the C3 watchdog timer and the interactions between the two.
    - Moved right hand ground cut switch to vbat switch. This solves a *lot* of problems with removing the ground and shutdown not working correctly.
    - Got rid of "fast charge" and split the charge / discharge paths with independent PTC (5A out, 2A in).
    - Switched most everytthing to 100k. 1M wasn't enough to overcome leakage, and 10k was too much.
    - Fixed the ablic bypass cap which should have gone right to VDD.
    - Rerouted !SD for lots of paranoia.
2021-03-01 Full update of the BOM; added non PCB materials including the heaters, thermistors. Updated fuses to be decent PTCs. Might regret that later, but it really seems like the right thing.
2021-03-17 Upped battery board to v2.1. No real changes, besides adding fiducials (blargh!), updating the board version, and adding the flight marker to TPLACE.
    More importantly, the BOM has been upadated to reflect what Screaming Circuits is going to stuff for us.
2021-03-27 Updated shutdown mosfet resistors to 100k after the battery failed quiescent power draw, and removed backup thermistors from the BOM.
2021-04-09 OreSat Battery Card v2.1
    - Shrunk fastener foot prints to gain more room.
    - Redid DF3 switch layouts to get the jumper wires closer to the switche's mini-contact holes.
    - Added fiducials.
    - Replaced quad N channel MOSFET with four N channels because the quad pack is unobtainium right now.
2021-04-20 Fixed off by one on BOM
2021-10-07 Update README.md
    Link to google doc
2021-11-09 Battery v3.0. Might actually work, and with less dropouts.
2021-11-09 v3.0 sent off to fab! Updated BOM, and committed final changes to card. Lots of small changes, including better power routing, resistors in the UART line to the C3, and as mentioned in an earlier com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
2021-12-29 Added inhibit block diagram schematic and PDF.
2022-01-28 Updated inhibit switch diagram to be more compact, reflect Nanoracks SDT call outs
2022-07-13 Migrated to KiCad
2022-07-28 Fixed a ton of DRC errors, maybe found some problems
2022-07-28 The DRC is happy now
2022-07-29 Fixed the voltage regulator problem, and the DRC is happy
2023-06-18 Updated kicad import of battery card v3.0
2023-12-02 Updating KiCAD import of EAGLE battery card v3.0 and calling it v3.1 because the gerber files will definitely be different and we'll probably implement a few small changes. Reimports, renames, and fi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
2023-12-02 Updated readme and picture.
2023-12-02 Minor fix to README
2023-12-02 Maybe it's better if there's not an extra copy of the KiCAD import files?
2023-12-02 Kicad import try #3. Now with DXFs from custom EAGLE layers. Schematic worksheets and names updated.
2023-12-02 Move main connector to kicad libraries; start updating text size.
2023-12-02 Transferred connector page to oresat-kicad. Added correct card outline.
2023-12-03 Updated ground planes, battery foot prints, zones needs more work.
2023-12-03 better schematic layout (no netlist changes) on battery packs, and updated DRUs and fixed some minor DRU issues.
2024-01-04 Adding MLI template v1.0
2024-01-04 Expanded a few mm to catch more battery area
2024-01-04 Add some external dimensions
2024-01-05 README now links to PCBA and assembly BOMs.
2024-01-05 Update README.md
    Link to OnShape
2025-12-27 Added NASA ISS Safety Committee approved inhibits block diagram
2026-01-11 Starting Battery Card 4.0
    Changed root sheet to hierarchical sheet. No change to schematic or layout yet. Updated the stackup with oresat template. Switched to variables for version and date.
2026-01-11 Minor polishing, removing outdated OPD signals and OPD power jumper.
2026-01-11 Added +battery disconect mosfet and switch
2026-01-11 Negative battery disconnects in. Ready for KiCad component upgrade.
2026-01-14 Renovated Schematic
    Updated schematic symbols and made more uniform with changed resistor, capacitor, and FET symbols. Changed 0603 cap foot print to 0603 small in Oresat passives. Added 2 new resistors and 2 new caps i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
2026-02-01 Progress on v4
    Figure out to bypass negative battery cutoff with 10k to make sure that nSHUTDOWN always works. Lots of moving around (it's tight), finally got pack 1 done. Working on the Pack 2.
2026-02-02 Progress on battery card v4
    Moved in -batt cutoffs, which caused a lot of pain and suffering. Started updating BOM, and fixed all transistor packages. Updated resistor packages, too. Still needs a lot of cleanup, but probably 8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
2026-02-03 Routing complete!
2026-02-03 Updated BOM, ready for polish and switch to MCXN
2026-03-12 Test out shallow clone
    Git demonstration
2026-03-23 Not sure what changed from back in February, but committing anyway :)
2026-03-23 Updated data, spiffed up the root page, renamed some STM specific OPD signals, synced SCH and BRD, fixed a bunch of DRC errors, NOW ready for MCXN import that will screw everything up.
2026-03-23 Added MCXN. Preliminary power layout, started removal of old symbols and footprints.
2026-04-05 Routed unconnected lines - needs DRC fixes and review
2026-04-05 Cleaned Up DRC errors & silkscreen
    Should be good? Needs review. Only 2 warnings left, "isolated copper fill" for zones Q36-D etc...
2026-05-14 Updated gitignore file for KiCad 10
2026-05-14 Revision 2.1 of the OreSat1 battery inhibits block diagram. Committing PDF for posterity
2026-05-14 Intermediary state on v4. Added one of two efuses.
2026-06-05 Schematic complete with new TPS circuit breaker; layout in progress

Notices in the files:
parts and their libraries:
SparkFun-Connectors: Licensing: Creative Commons ShareAlike 4.0 International - https://creativecommons.org/licenses/by-sa/4.0
COPYRIGHT: Copyright (C) 2021 Ultra Librarian. All rights reserved.
